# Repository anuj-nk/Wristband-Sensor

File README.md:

# ThrowSense  
*A wearable system that measures throw speed and estimates throw distance, visualized through a physical stepper-motor gauge and an OLED display.*

---

## Project Overview

ThrowSense is a two-device interactive system consisting of a wearable sensing unit and a handheld or desk-mounted display unit. The wearable tracks the motion of a throw using inertial sensors and computes an estimated throw speed and distance. The display device presents this information using a physical needle gauge driven by a stepper motor, along with an OLED screen for numeric readouts and mode selection.

The system is designed to provide intuitive, glanceable feedback for different throwing contexts (e.g., football, baseball), emphasizing physical interaction and real-world sensing over screen-only visualization.

### General Physical Sketch

---

## Sensing Device — Wearable Motion Tracker

### Device Overview

The sensing device is a wrist- or forearm-mounted wearable that captures high-frequency motion data during a throwing action. It detects when a throw occurs, estimates release velocity, and performs lightweight DSP and physics-based calculations before transmitting results to the display device.

### Hardware Components

- **Processor:** ESP32-C3
- **IMU Sensor:** MPU-6050  
  - 3-axis accelerometer  
  - 3-axis gyroscope  
- **Power:**  
  - 3.7V LiPo battery  

### Part Numbers

- ESP32-C3  
- MPU-6050

### How It Works

1. The MPU-6050 continuously samples acceleration and angular velocity.
2. Motion data is filtered and analyzed in real time to detect a throwing event.
3. Peak angular velocity and acceleration are extracted during the throw.
4. Release speed is estimated from IMU data.
5. A simplified physics-based model estimates throw distance based on:
   - selected object type (e.g., football, baseball)
   - assumed release angle
   - object-specific parameters (mass, drag heuristic).
6. Final computed values are transmitted to the display device.

### Sensor Device Sketch

---

## Display Device — Physical Gauge + OLED Interface

### Device Overview

The display device is a handheld or desk-mounted physical interface that presents throw data in both analog and digital forms. A stepper-motor-driven needle provides an immediate visual indication of throw speed, while an OLED display shows numeric values and the selected throw mode. A button allows the user to cycle through object types before throwing.

### Hardware Components

- **Processor:** ESP32-C3
- **Stepper Motor:** 28BYJ-48
- **Stepper Driver:** ULN2003
- **Display:** 0.96" I2C OLED (SSD1306)
- **User Input:** Tactile push button
- **Indicator:** Status LED
- **Power:** Wall power or battery (TBD)

### Part Numbers

- ESP32-C3  
- 28BYJ-48 Stepper Motor  
- ULN2003 Driver Board  
- SSD1306 OLED Display  

### How It Works

1. The display device receives processed throw data from the sensing device.
2. The stepper motor rotates the needle to a mapped angle corresponding to throw speed.
3. The OLED displays:
   - selected throw mode (e.g., football, baseball)
   - measured throw speed
   - estimated throw distance
4. The user presses a button to cycle through throw modes.
5. Mode changes are sent back to the sensing device to update calculation parameters.
6. The status LED indicates system state:
   - **Ready:** system prepared to detect a throw  
   - **Throwing:** motion detected  
   - **Processing:** calculations in progress  

### Display Device Sketch

---

## Device Communication & System Architecture

### Device Communication

- **Communication medium:** To be determined (wired or wireless)
- **Topology:** Sensing device → Display device
- The sensing device performs all DSP and physics calculations.
- The display device focuses on visualization and user interaction.

### System Diagram — High-Level Communication

### System Diagram — Data Flow

**Data Flow Explanation:**

1. Raw IMU data is captured on the sensing device.
2. DSP techniques (filtering, thresholding, peak detection) identify a throw.
3. A physics-based model estimates speed and distance.
4. Final metrics are transmitted to the display device.
5. The display device maps speed to motor position and updates the OLED and LED indicators.

## Datasheets

All datasheets are included in the `/datasheets` directory, including:

- ESP32-C3 datasheet  
- MPU-6050 datasheet  
- 28BYJ-48 stepper motor datasheet  
- ULN2003 driver datasheet  
- SSD1306 OLED datasheet

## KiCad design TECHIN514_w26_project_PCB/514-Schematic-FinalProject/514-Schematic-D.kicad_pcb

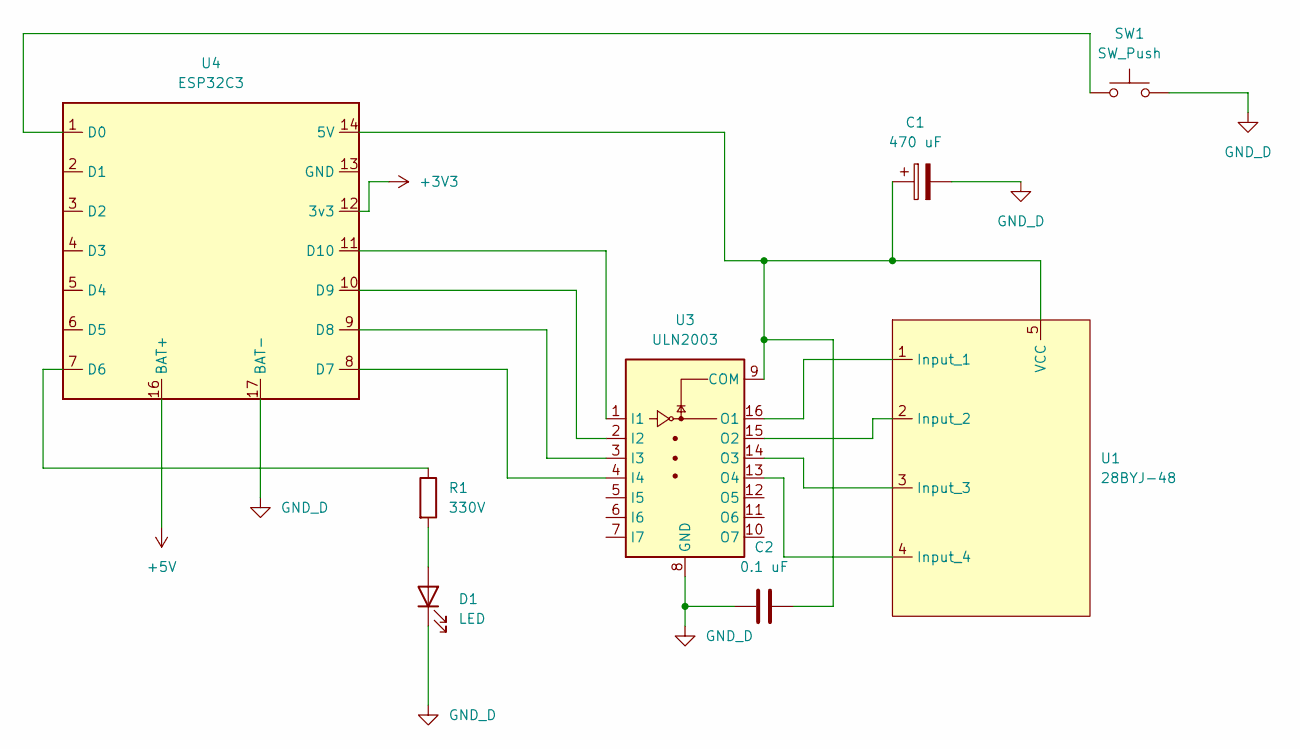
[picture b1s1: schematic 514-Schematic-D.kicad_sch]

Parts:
C1: 470 uF; C_0603_1608Metric_Pad1.08x0.95mm_HandSolder
C2: 0.1 uF; C_0603_1608Metric_Pad1.08x0.95mm_HandSolder
D1: LED; LED_0603_1608Metric_Pad1.05x0.95mm_HandSolder
R1: 330V; R_0603_1608Metric_Pad0.98x0.95mm_HandSolder
SW1: SW_Push; SW_PUSH_6mm
U1: 28BYJ-48; JST_XH_B5B-XH-AM_1x05_P2.50mm_Vertical
U3: ULN2003; DIP-16_W7.62mm
U4: ESP32C3; MCU_Seeed_ESP32C3

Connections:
+3V3: U4.12 (3v3)
+5V: U4.16 (BAT+)
GND_D: C1.2, C2.1, D1.1 (K), SW1.2, U3.8 (GND), U4.17 (BAT-)
unnamed: D1.2 (A), R1.2
unnamed: U1.1 (Input_1), U3.16 (O1)
unnamed: U1.2 (Input_2), U3.15 (O2)
unnamed: U1.3 (Input_3), U3.14 (O3)
unnamed: U1.4 (Input_4), U3.13 (O4)
unnamed: C1.1, C2.2, U1.5 (VCC), U3.9 (COM), U4.14 (5V)
unnamed: U3.1 (I1), U4.11 (D10)
unnamed: U3.2 (I2), U4.10 (D9)
unnamed: U3.3 (I3), U4.9 (D8)
unnamed: U3.4 (I4), U4.8 (D7)
unnamed: SW1.1, U4.1 (D0)
unnamed: R1.1, U4.7 (D6)

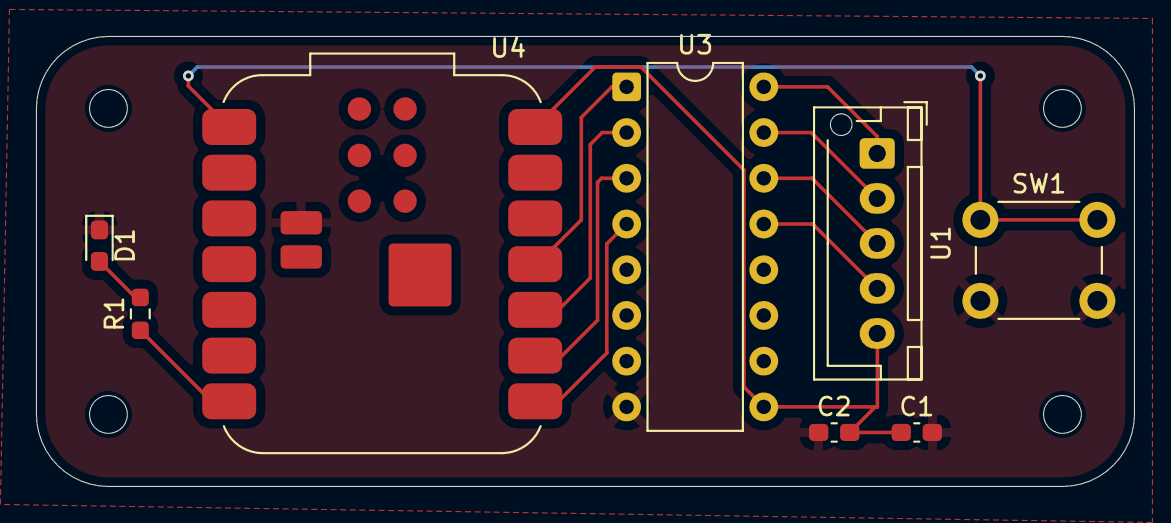
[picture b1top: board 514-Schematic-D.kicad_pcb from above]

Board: 2 copper layers, 61.0 x 25.0 mm, 8 parts (0 on the bottom side), 13 nets.

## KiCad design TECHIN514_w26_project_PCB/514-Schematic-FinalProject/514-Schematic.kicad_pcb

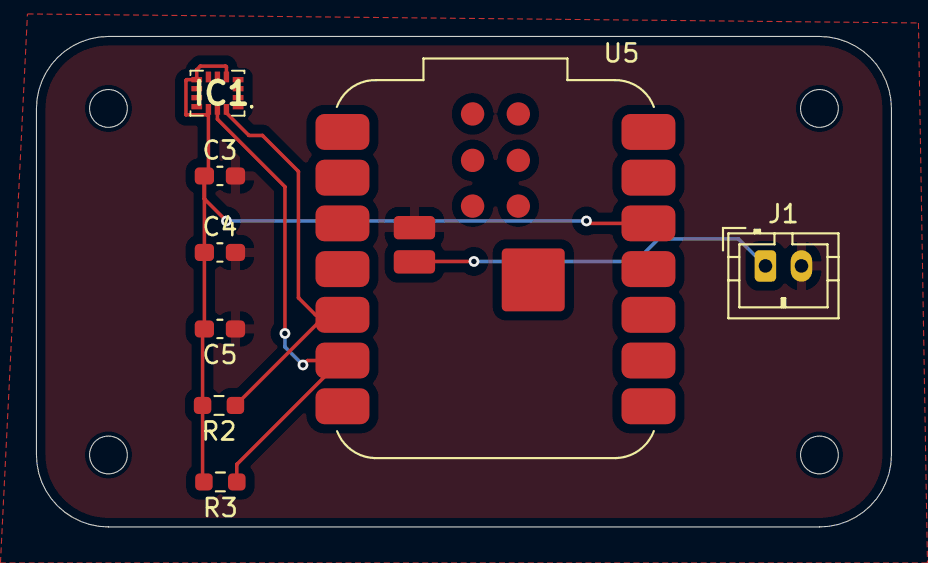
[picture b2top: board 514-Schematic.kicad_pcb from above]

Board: 2 copper layers, 47.5 x 27.2 mm, 8 parts (0 on the bottom side), 5 nets.

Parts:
C3: 0.1 uF; C_0603_1608Metric_Pad1.08x0.95mm_HandSolder
C4: 2.2 uF; C_0603_1608Metric_Pad1.08x0.95mm_HandSolder
C5: 10 nF; C_0603_1608Metric_Pad1.08x0.95mm_HandSolder
IC1: ICM-42670-P; ICM42670P
J1: Conn_01x02; JST_PH_B2B-PH-K_1x02_P2.00mm_Vertical
R2, R3: 10 kΩ; R_0603_1608Metric_Pad0.98x0.95mm_HandSolder
U5: ESP32C3; MCU_Seeed_ESP32C3

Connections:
GND: C3.2, C4.2, C5.1, IC1.1 (AP_SDO_/_AP_AD0), IC1.6 (GND), IC1.7 (FSYNC), J1.2, U5.17 (BAT-)
unnamed: C3.1, C4.1, C5.2, IC1.5 (VDDIO), IC1.8 (VDD), IC1.12 (AP_CS), R2.2, R3.2, U5.12 (3v3)
unnamed: IC1.13 (AP_SCL_/_AP_SCLK), R3.1, U5.6 (D5)
unnamed: IC1.14 (AP_SDA_/_AP_SDIO_/_AP_SDI), R2.1, U5.5 (D4)
unnamed: J1.1, U5.16 (BAT+)

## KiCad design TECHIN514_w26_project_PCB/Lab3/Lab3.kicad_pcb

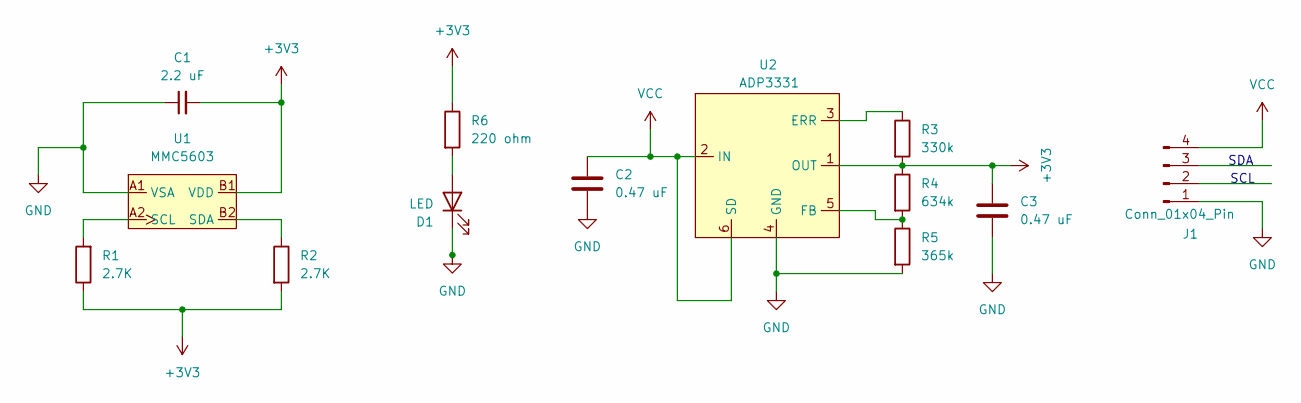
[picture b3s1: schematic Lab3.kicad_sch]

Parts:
C1: 2.2 uF; C_0603_1608Metric_Pad1.08x0.95mm_HandSolder
C2, C3: 0.47 uF; C_0603_1608Metric_Pad1.08x0.95mm_HandSolder
D1: LED; LED_0603_1608Metric_Pad1.05x0.95mm_HandSolder
J1: Conn_01x04_Pin; PinSocket_1x04_P2.54mm_Vertical
R1, R2: 2.7K; R_0603_1608Metric_Pad0.98x0.95mm_HandSolder
R3: 330k; R_0603_1608Metric_Pad0.98x0.95mm_HandSolder
R4: 634k; R_0603_1608Metric_Pad0.98x0.95mm_HandSolder
R5: 365k; R_0603_1608Metric_Pad0.98x0.95mm_HandSolder
R6: 220 ohm; R_0603_1608Metric_Pad0.98x0.95mm_HandSolder
U1: MMC5603; XDCR_MMC5603NJ
U2: ADP3331; SOT-23-6_Handsoldering

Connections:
+3V3: C1.2, C3.1, R1.1, R2.2, R3.2, R4.1, R6.1, U1.B1 (VDD), U2.1 (OUT)
GND: C1.1, C2.2, C3.2, D1.1 (K), J1.1, R5.2, U1.A1 (VSA), U2.4 (GND)
unnamed: D1.2 (A), R6.2
unnamed: R1.2, U1.A2 (SCL)
unnamed: R2.1, U1.B2 (SDA)
unnamed: R3.1, U2.3 (ERR)
unnamed: R4.2, R5.1, U2.5 (FB)
VCC: C2.1, J1.4, U2.2 (IN), U2.6 (SD)

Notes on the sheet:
SDA
SCL

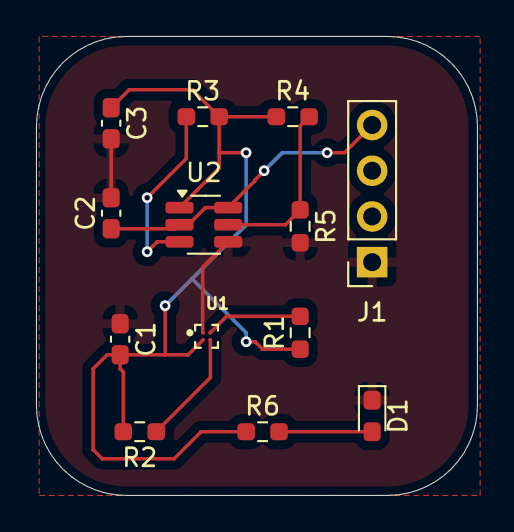
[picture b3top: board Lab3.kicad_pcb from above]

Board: 2 copper layers, 24.5 x 25.5 mm, 13 parts (0 on the bottom side), 8 nets.

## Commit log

2026-01-20 Added README
2026-01-20 Added Datasheets
2026-01-20 Add images to README for system sketches
    Updated README to include images for various system components.
2026-01-27 Revise system diagrams in README
    Updated system diagrams and replaced image links with a PDF link.
2026-01-27 Update print statement from 'Hello' to 'Goodbye'
2026-01-27 Revert "Update print statement from 'Hello' to 'Goodbye'"
    This reverts commit 0b9ea3a7ffee00b22fced410a536641664c64975.
2026-01-27 Update data flow diagram in README
    Replaced link to PDF with an image of the schematic.
2026-01-29 Added project files and screenshots to github for Lab3
2026-01-30 Added Manufacturing FIles (Gerber and Drill)
    Although there are no drill holes in this diagram
2026-02-02 Added final personal PCB files
    Excluding PCB files for Gerber and actual Manufacturing.
2026-03-02 Add PCB and Code for Devices
2026-03-15 Added updated code for both Sensing and Display Device
